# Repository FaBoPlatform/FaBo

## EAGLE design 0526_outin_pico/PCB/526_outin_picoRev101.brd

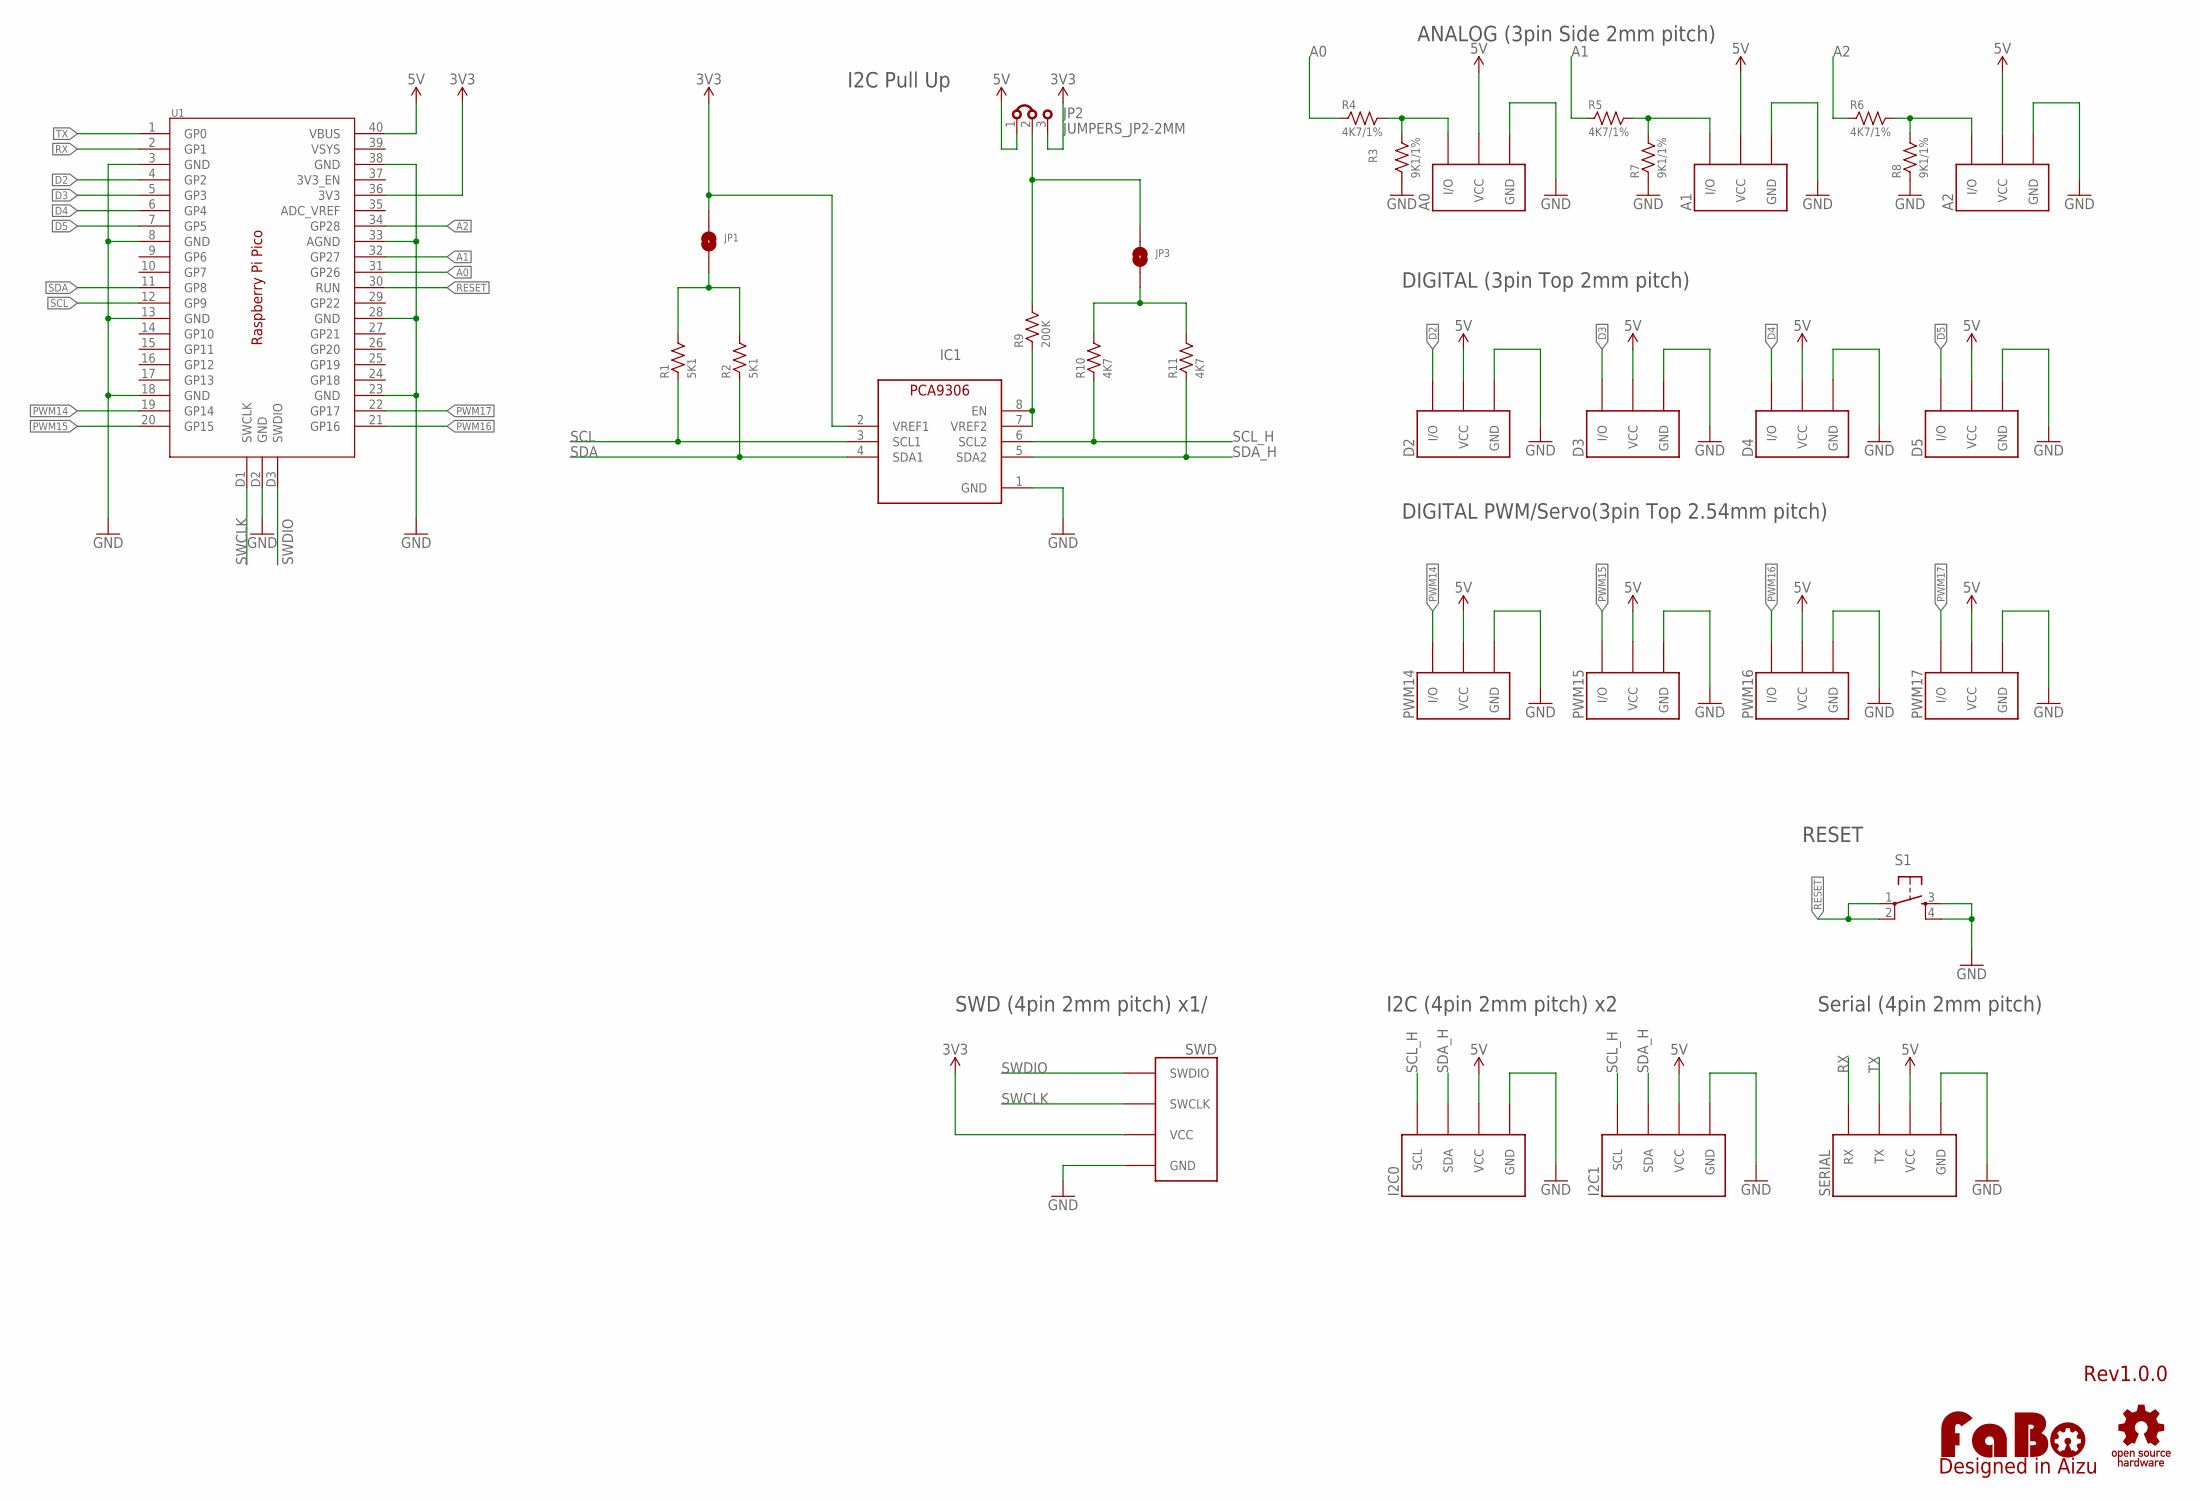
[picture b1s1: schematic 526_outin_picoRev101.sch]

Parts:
A0, A1, A2: FABO_BRICK_3PIN-S03B-PASK-2_LONG; FABO_BRICK_3PIN_S03B-PASK-2_LONG
D2, D3, D4, D5: FABO_BRICK_3PIN-B03B-PASK-1; FABO_BRICK_3PIN_B03B-PASK-1
I2C0, I2C1: FABO_BRICK_I2C-B04B-PASK-1; FABO_BRICK_I2C_B04B-PASK-1
IC1: PCA9306_SSOP; 8PIN-SSOP
JP1, JP3: SMD-JUMPER-2_SHORT; SMD-JUMPER-2-SHORT
JP2: JUMPERS_JP2-2MM
LOGO1: LOGO_OSHW-M_BOTTOM; LOGO_OSHW_M_BOTTOM
LOGO2: LOGO_FABO-M; LOGO_FABO_M
PWM14, PWM15, PWM16, PWM17: FABO_BRICK_3PIN-HEADER; FABO_BRICK_3PIN_HEADER
R1, R2: 5K1; 0603
R3, R7, R8: 9K1/1%; 0603
R4, R5, R6: 4K7/1%; 0603
R9: 200K; 0603
R10, R11: 4K7; 0603
S1: TACT-SWITCH-6MM; DTS_6_V
SERIAL: FABO_BRICK_SERIAL-B04B-PASK-1; FABO_BRICK_SERIAL_B04B-PASK-1
SWD: FABO-SWD-4PIN; FABO_BRICK_SWD_B04B-PASK-1_SILK
U1: RASPBERRY_PI_PICO; RASPBERRY_PI_PICO_SMD

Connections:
3V3: IC1.2 (VREF1), JP1.1, JP2.3, SWD.VCC, U1.36 (3V3)
5V: A0.VCC, A1.VCC, A2.VCC, D2.VCC, D3.VCC, D4.VCC, D5.VCC, I2C0.VCC, I2C1.VCC, JP2.1, PWM14.VCC, PWM15.VCC, PWM16.VCC, PWM17.VCC, SERIAL.VCC, U1.40 (VBUS)
A0: R4.1, U1.31 (GP26)
A1: R5.1, U1.32 (GP27)
A2: R6.1, U1.34 (GP28)
D2: D2.I/O, U1.4 (GP2)
D3: D3.I/O, U1.5 (GP3)
D4: D4.I/O, U1.6 (GP4)
D5: D5.I/O, U1.7 (GP5)
GND: A0.GND, A1.GND, A2.GND, D2.GND, D3.GND, D4.GND, D5.GND, I2C0.GND, I2C1.GND, IC1.1 (GND), PWM14.GND, PWM15.GND, PWM16.GND, PWM17.GND, R3.1, R7.1, R8.1, S1.3, S1.4, SERIAL.GND, SWD.GND, U1.3 (GND), U1.8 (GND), U1.13 (GND), U1.18 (GND), U1.23 (GND), U1.28 (GND), U1.33 (AGND), U1.38 (GND), U1.D2 (GND)
unnamed: A0.I/O, R3.2, R4.2
unnamed: A1.I/O, R5.2, R7.2
unnamed: JP1.2, R1.2, R2.2
unnamed: A2.I/O, R6.2, R8.2
unnamed: JP2.2, JP3.1, R9.2
unnamed: JP3.2, R10.2, R11.2
unnamed: IC1.7 (VREF2), IC1.8 (EN), R9.1
PWM14: PWM14.I/O, U1.19 (GP14)
PWM15: PWM15.I/O, U1.20 (GP15)
PWM16: PWM16.I/O, U1.21 (GP16)
PWM17: PWM17.I/O, U1.22 (GP17)
RESET: S1.1, S1.2, U1.30 (RUN)
RX: SERIAL.RX, U1.2 (GP1)
SCL: IC1.3 (SCL1), R1.1, U1.12 (GP9)
SCL_H: I2C0.SCL, I2C1.SCL, IC1.6 (SCL2), R10.1
SDA: IC1.4 (SDA1), R2.1, U1.11 (GP8)
SDA_H: I2C0.SDA, I2C1.SDA, IC1.5 (SDA2), R11.1
SWCLK: SWD.SWCLK, U1.D1 (SWCLK)
SWDIO: SWD.SWDIO, U1.D3 (SWDIO)
TX: SERIAL.TX, U1.1 (GP0)

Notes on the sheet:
Rev1.0.0
DIGITAL (3pin Top 2mm pitch)
ANALOG (3pin Side 2mm pitch)
DIGITAL PWM/Servo(3pin Top 2.54mm pitch)
I2C (4pin 2mm pitch) x2
Serial (4pin 2mm pitch)
RESET
I2C Pull Up
SWD (4pin 2mm pitch) x1/

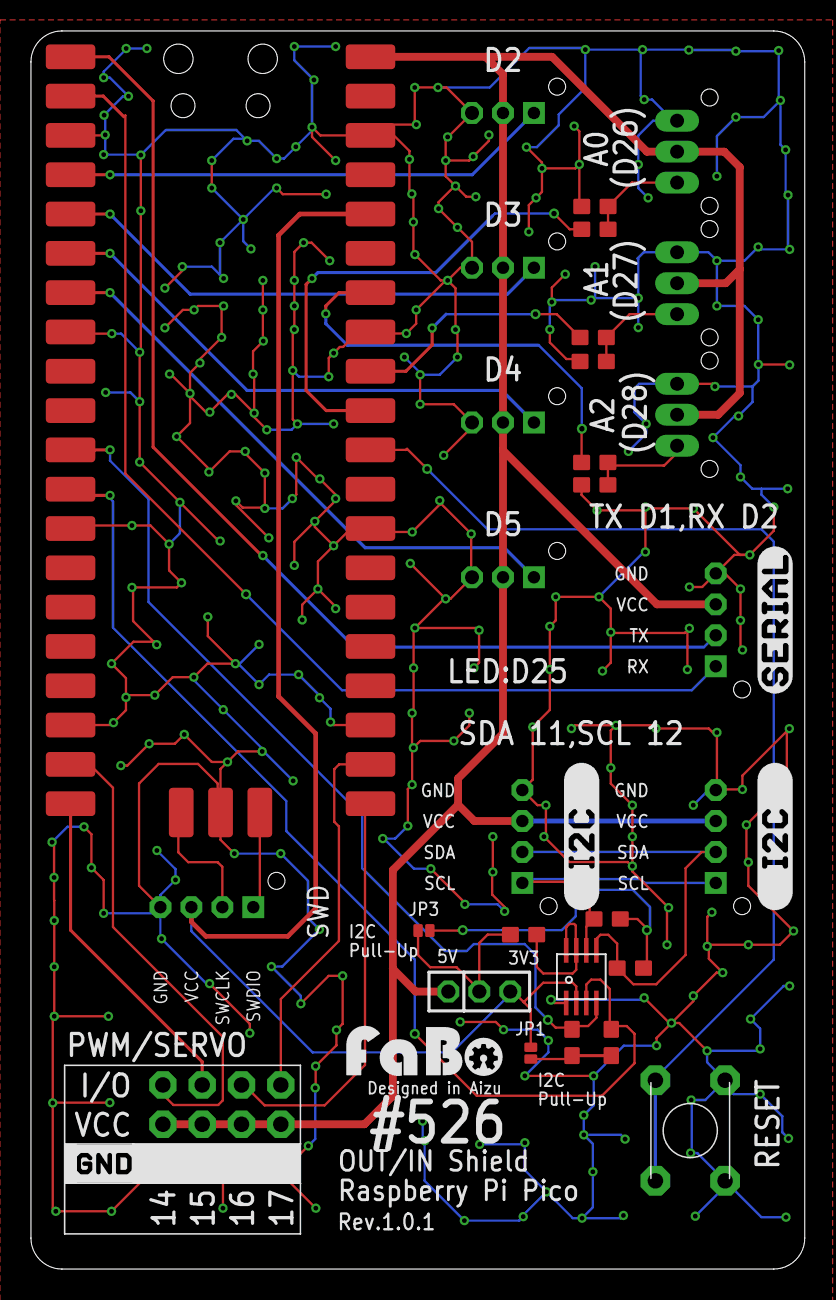
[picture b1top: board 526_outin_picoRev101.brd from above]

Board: 2 copper layers, 50.0 x 80.0 mm, 38 parts (0 on the bottom side), 30 nets.

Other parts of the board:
U$2: LOGO_SILK_SERIAL2
U$11, U$12: LOGO_SILK_I2C
U$19: LOGO_SILK_GND

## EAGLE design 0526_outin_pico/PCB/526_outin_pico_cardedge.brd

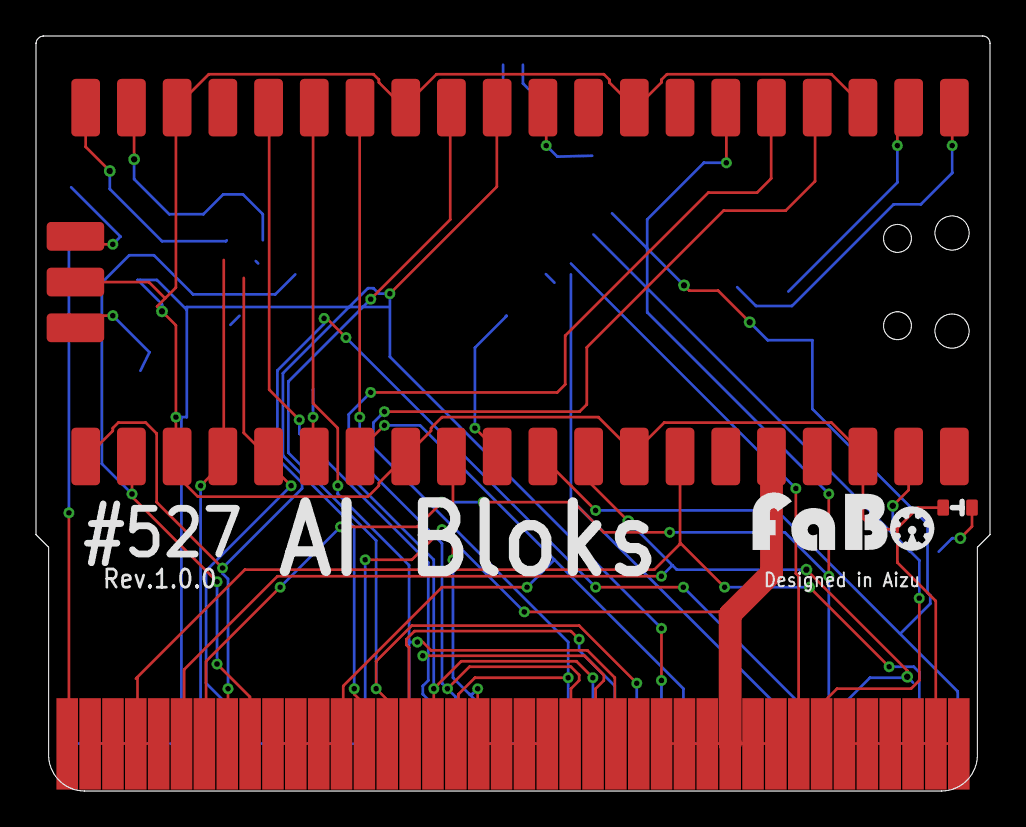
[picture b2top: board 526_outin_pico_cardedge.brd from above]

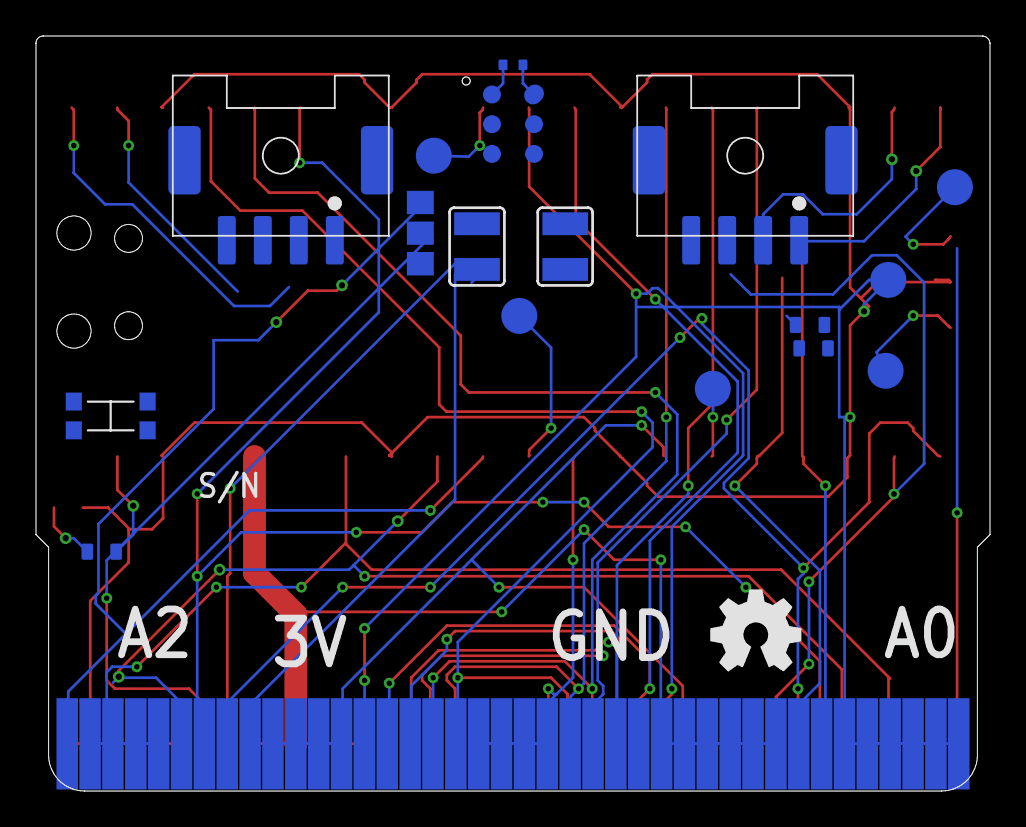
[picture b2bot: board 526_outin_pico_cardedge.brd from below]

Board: 2 copper layers, 53.0 x 41.9 mm, 22 parts (17 on the bottom side), 34 nets.

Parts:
C1: 0.1uF; 0402
CN1, CN2: SM04B-PASS
GP7: TPSQTP20R; TP20R
JMP1: 0R-JUMPA; A0R-JMP
LED1: 0603
LOGO1: LOGO_OSHW_M_BOTTOM
LOGO2: LOGO_FABO_M
R1: 470; 0603
R2, R3: 0603
S2: KMR2
SJ1, SJ2: SJW
TP1, TP2, TP3, TP4, TP10: TPSQTP20R; TP20R
U1: RASPBERRY_PI_PICO_SMD
U$1: SPM0405H; SPM4050
U$2: BBC_EDGE

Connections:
3V3: C1.2, CN1.3, CN2.3, JMP1.1, R2.2, R3.2, U1.36, U$1.6:VDD, U$2.P$27, U$2.P$28, U$2.P$29, U$2.P$30, U$2.P$31, U$2.P$32, U$2.P$67, U$2.P$68, U$2.P$69, U$2.P$70, U$2.P$71, U$2.P$72
A0: U1.31, U$2.P$1, U$2.P$41
A1: U1.32, U$2.P$6, U$2.P$46
A2: U1.34, U$2.P$2, U$2.P$3, U$2.P$4, U$2.P$5, U$2.P$42, U$2.P$43, U$2.P$44, U$2.P$45
D2: U1.4, U$2.P$18, U$2.P$58
D3: U1.5, U$2.P$17, U$2.P$57
D4: U1.6, U$2.P$7, U$2.P$47
D8: U1.11, U$2.P$14, U$2.P$54
D9_LEDS: U1.12, U$2.P$15, U$2.P$55
GND: C1.1, CN1.4, CN2.4, JMP1.3, LED1.CATHODE, S2.3, S2.4, TP3.TP, U1.3, U1.8, U1.13, U1.18, U1.23, U1.28, U1.33, U1.38, U1.D2, U$1.1:GND, U$1.3:GND, U$2.P$35, U$2.P$36, U$2.P$37, U$2.P$38, U$2.P$39, U$2.P$40, U$2.P$75, U$2.P$76, U$2.P$77, U$2.P$78, U$2.P$79, U$2.P$80
GP14: CN2.2, U1.19
GP15: CN2.1, U1.20
GP16: U$2.P$16, U$2.P$56
GP16_PWM_UART0_TX: U1.21, U$2.P$8, U$2.P$48
GP17_PWM_UART0_RX: U1.22, U$2.P$9, U$2.P$49
I2C1_SCL: R2.1, U1.25, U$2.P$33, U$2.P$73
I2C1_SDA: R3.1, U1.24, U$2.P$34, U$2.P$74
unnamed: R1.1, U1.39
unnamed: LED1.ANODE, R1.2
unnamed: GP7.TP, U1.10
unnamed: TP10.TP, U1.26
unnamed: JMP1.2, U$1.2:LEFT/RIGHT
unnamed: SJ1.1, U$1.4:CLOCK
unnamed: SJ2.1, U$1.5:DATA
PDM_CLK: SJ1.2, U1.27, U$2.P$10, U$2.P$11, U$2.P$12, U$2.P$13, U$2.P$50, U$2.P$51, U$2.P$52, U$2.P$53
PDM_DIN: SJ2.2, U1.29, U$2.P$19, U$2.P$20, U$2.P$21, U$2.P$22, U$2.P$59, U$2.P$60, U$2.P$61, U$2.P$62
RESET: S2.1, S2.2, TP4.TP, U1.30
RX: CN1.1, U1.2
SPI1_RX: U1.16, U$2.P$24, U$2.P$64
SPI1_SCK: U1.14, U$2.P$23, U$2.P$63
SPI1_TX: U1.15, U$2.P$25, U$2.P$65
SWCLK: TP1.TP, U1.D1
SWDIO: TP2.TP, U1.D3
TX: CN1.2, U1.1

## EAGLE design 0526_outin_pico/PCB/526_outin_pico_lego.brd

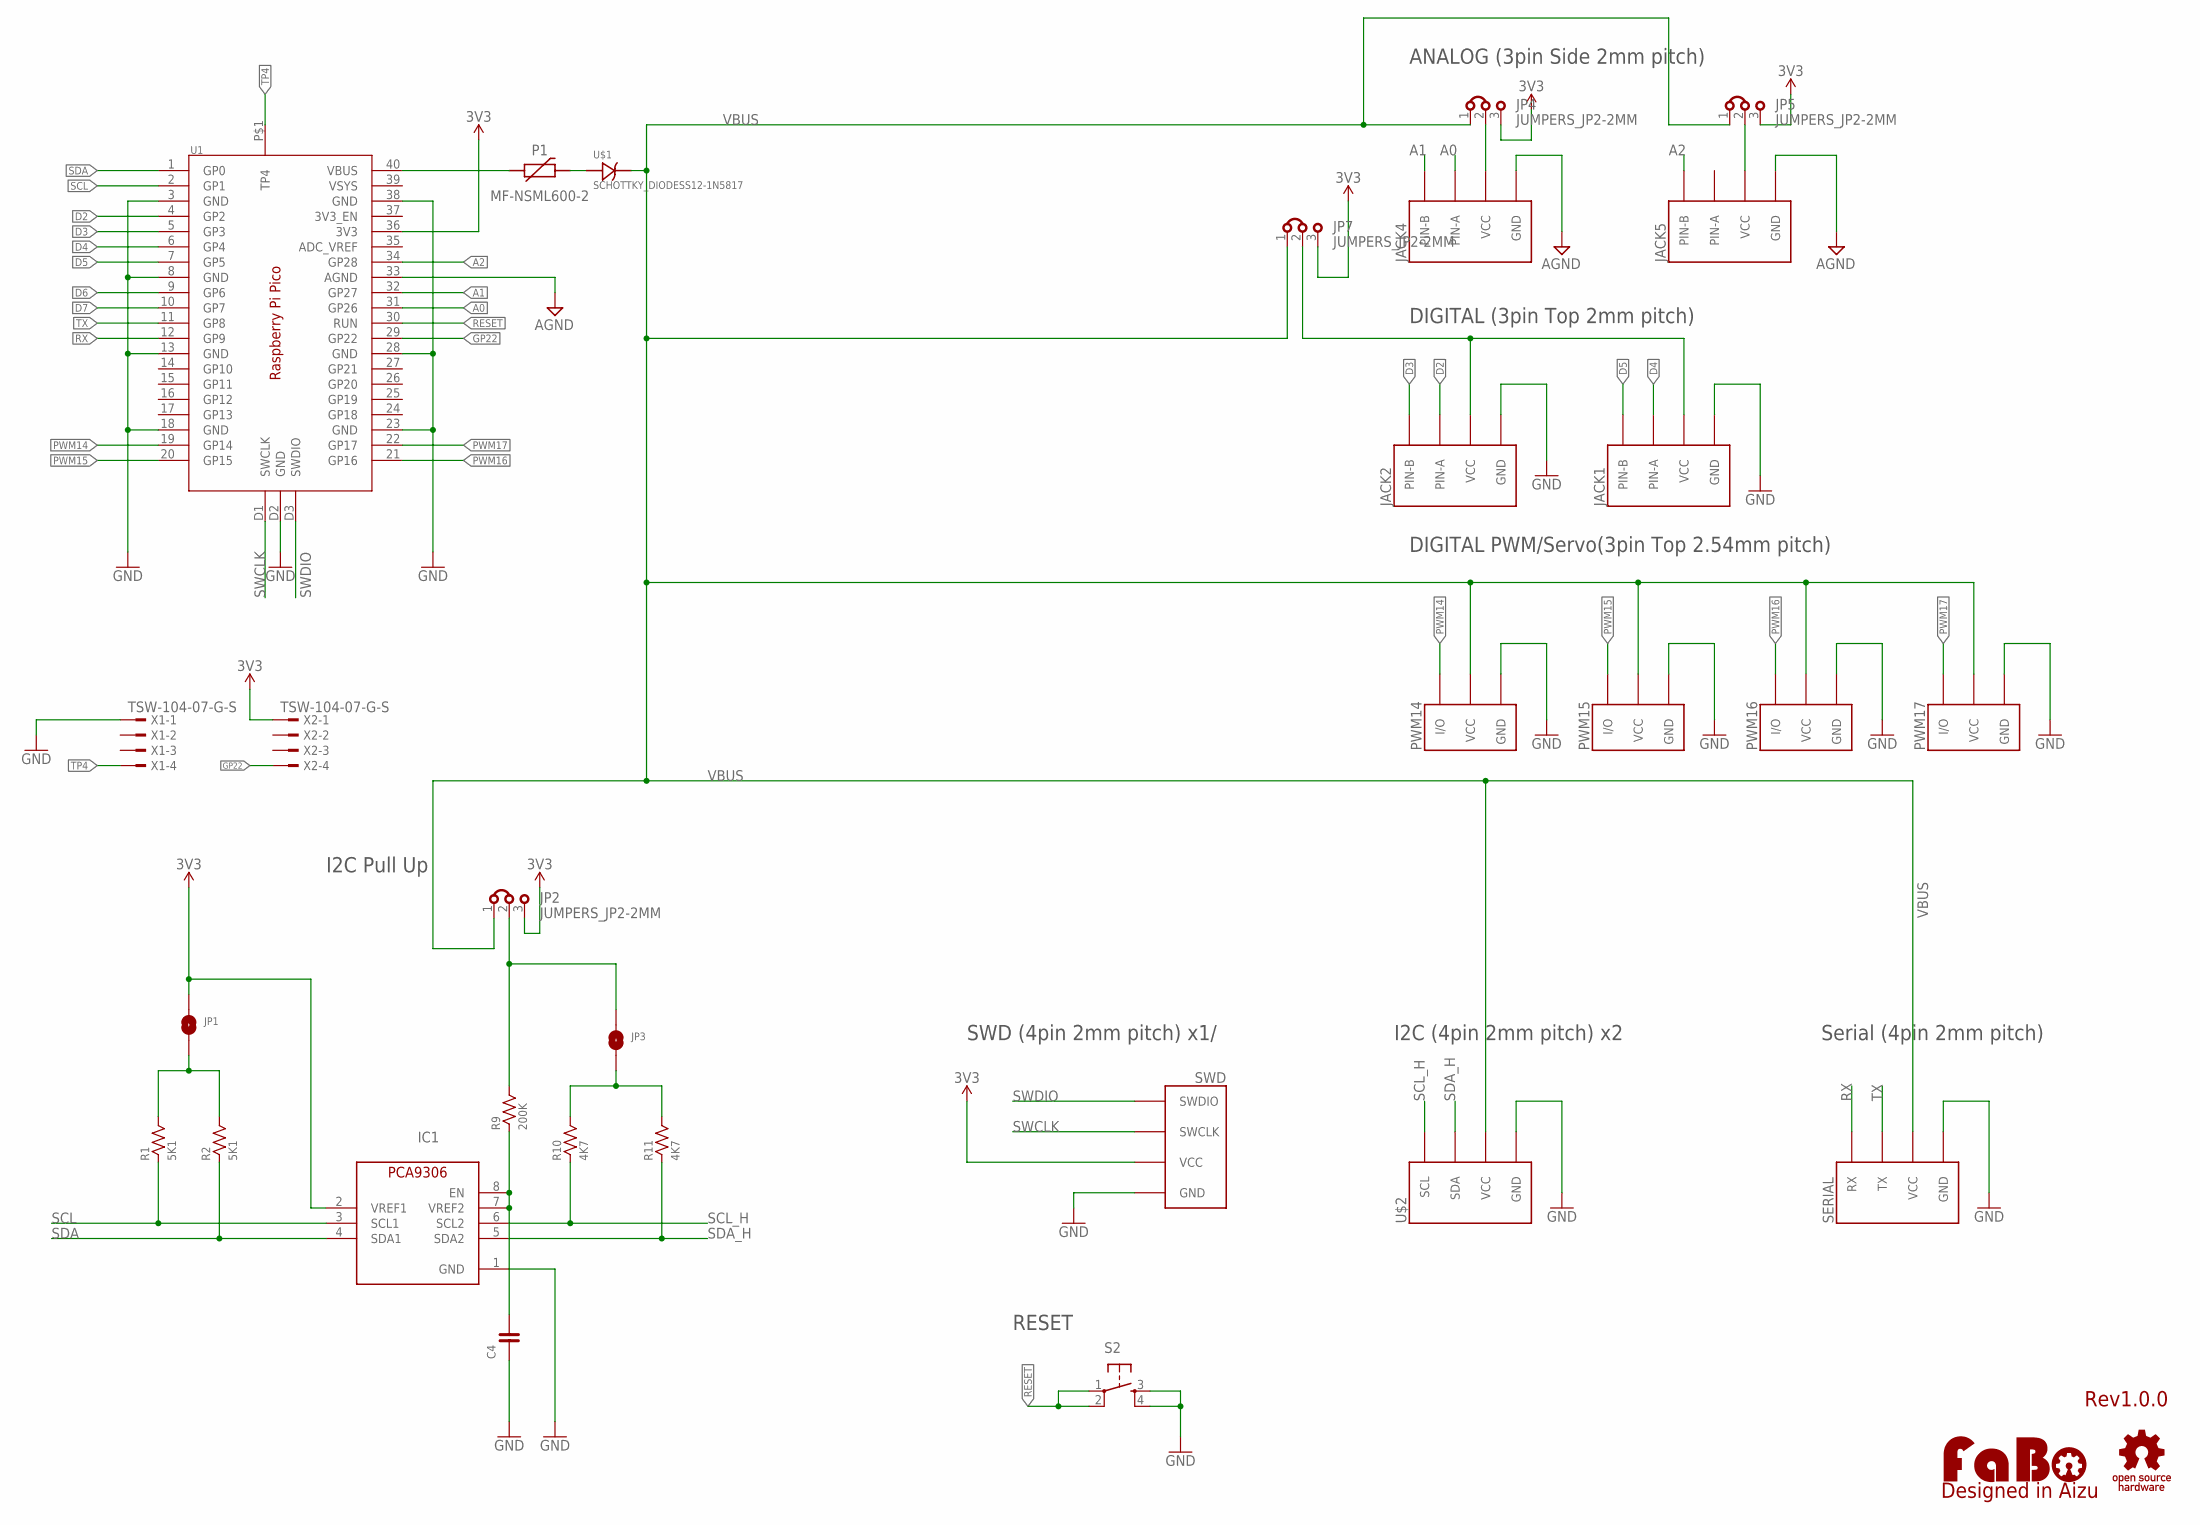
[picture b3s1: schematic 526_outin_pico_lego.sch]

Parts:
C4: CAPACITOR-0603_NARROW; 0603-NARROW
IC1: PCA9306_SSOP; 8PIN-SSOP
JACK1, JACK2, JACK4, JACK5: MODULAR-JACK-6P; 7002-6PXC-X
JP1, JP3: SMD-JUMPER-2_SHORT; SMD-JUMPER-2-SHORT
JP2, JP4, JP5, JP7: JUMPERS_JP2-2MM
LOGO1: LOGO_OSHW-M_BOTTOM; LOGO_OSHW_M_BOTTOM
LOGO2: LOGO_FABO-M; LOGO_FABO_M
P1: MF-NSML600-2; 1206
PWM14, PWM15, PWM16, PWM17: FABO_BRICK_3PIN-HEADER; FABO_BRICK_3PIN_HEADER
R1, R2: 5K1; 0603
R9: 200K; 0603
R10, R11: 4K7; 0603
S2: TACT-SWITCH-SMD_KMR2; KMR2
SERIAL: FABO_BRICK_SERIAL-S04B-PASK-2_LONG; FABO_BRICK_SERIAL_S04B-PASK-2_LONG
SWD: FABO-SWD-4PIN; FABO_BRICK_SWD_B04B-PASK-1_SILK
U1: RASPBERRY_PI_PICORASPBERRY_PI_PICO_SMD_PDM; RASPBERRY_PI_PICO_SMD_PDM
U$1: SCHOTTKY_DIODESS12-1N5817; DO-214AC
U$2: MODULAR-JACK-6P-I2C; 7002-6PXC-X
X1, X2: TSW-104-07-G-S; TSW-104-XX-G-S

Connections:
3V3: IC1.2 (VREF1), JP1.1, JP2.3, JP4.3, JP5.3, JP7.3, SWD.VCC, U1.36 (3V3), X2.1
A0: JACK4.5 (PIN-A), U1.31 (GP26)
A1: JACK4.6 (PIN-B), U1.32 (GP27)
A2: JACK5.6 (PIN-B), U1.34 (GP28)
AGND: JACK4.1 (GND), JACK5.1 (GND), U1.33 (AGND)
D2: JACK2.5 (PIN-A), U1.4 (GP2)
D3: JACK2.6 (PIN-B), U1.5 (GP3)
D4: JACK1.5 (PIN-A), U1.6 (GP4)
D5: JACK1.6 (PIN-B), U1.7 (GP5)
D6: U1.9 (GP6)
D7: U1.10 (GP7)
GND: C4.1, IC1.1 (GND), JACK1.1 (GND), JACK2.1 (GND), PWM14.GND, PWM15.GND, PWM16.GND, PWM17.GND, S2.3, S2.4, SERIAL.GND, SWD.GND, U1.3 (GND), U1.8 (GND), U1.13 (GND), U1.18 (GND), U1.23 (GND), U1.28 (GND), U1.38 (GND), U1.D2 (GND), U$2.1 (GND), X1.1
GP22: U1.29 (GP22), X2.4
unnamed: JACK5.3 (VCC), JP5.2
unnamed: JP1.2, R1.2, R2.2
unnamed: JACK4.3 (VCC), JP4.2
unnamed: JACK1.3 (VCC), JACK2.3 (VCC), JP7.2
unnamed: P1.P$2 (2), U$1.CATHODE (ANODE)
unnamed: JP2.2, JP3.1, R9.2
unnamed: JP3.2, R10.2, R11.2
unnamed: C4.2, IC1.7 (VREF2), IC1.8 (EN), R9.1
PWM14: PWM14.I/O, U1.19 (GP14)
PWM15: PWM15.I/O, U1.20 (GP15)
PWM16: PWM16.I/O, U1.21 (GP16)
PWM17: PWM17.I/O, U1.22 (GP17)
RESET: S2.1, S2.2, U1.30 (RUN)
RX: SERIAL.RX, U1.12 (GP9)
SCL: IC1.3 (SCL1), R1.1, U1.2 (GP1)
SCL_H: IC1.6 (SCL2), R10.1, U$2.4 (SCL)
SDA: IC1.4 (SDA1), R2.1, U1.1 (GP0)
SDA_H: IC1.5 (SDA2), R11.1, U$2.5 (SDA)
SWCLK: SWD.SWCLK, U1.D1 (SWCLK)
SWDIO: SWD.SWDIO, U1.D3 (SWDIO)
TP4: U1.P$1 (TP4), X1.4
TX: SERIAL.TX, U1.11 (GP8)
VBUS: JP2.1, JP4.1, JP5.1, JP7.1, PWM14.VCC, PWM15.VCC, PWM16.VCC, PWM17.VCC, SERIAL.VCC, U$1.ANODE (CATHODE), U$2.3 (VCC)
VS: P1.P$1 (1), U1.40 (VBUS)

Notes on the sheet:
Rev1.0.0
DIGITAL (3pin Top 2mm pitch)
ANALOG (3pin Side 2mm pitch)
DIGITAL PWM/Servo(3pin Top 2.54mm pitch)
I2C (4pin 2mm pitch) x2
Serial (4pin 2mm pitch)
RESET
I2C Pull Up
SWD (4pin 2mm pitch) x1/

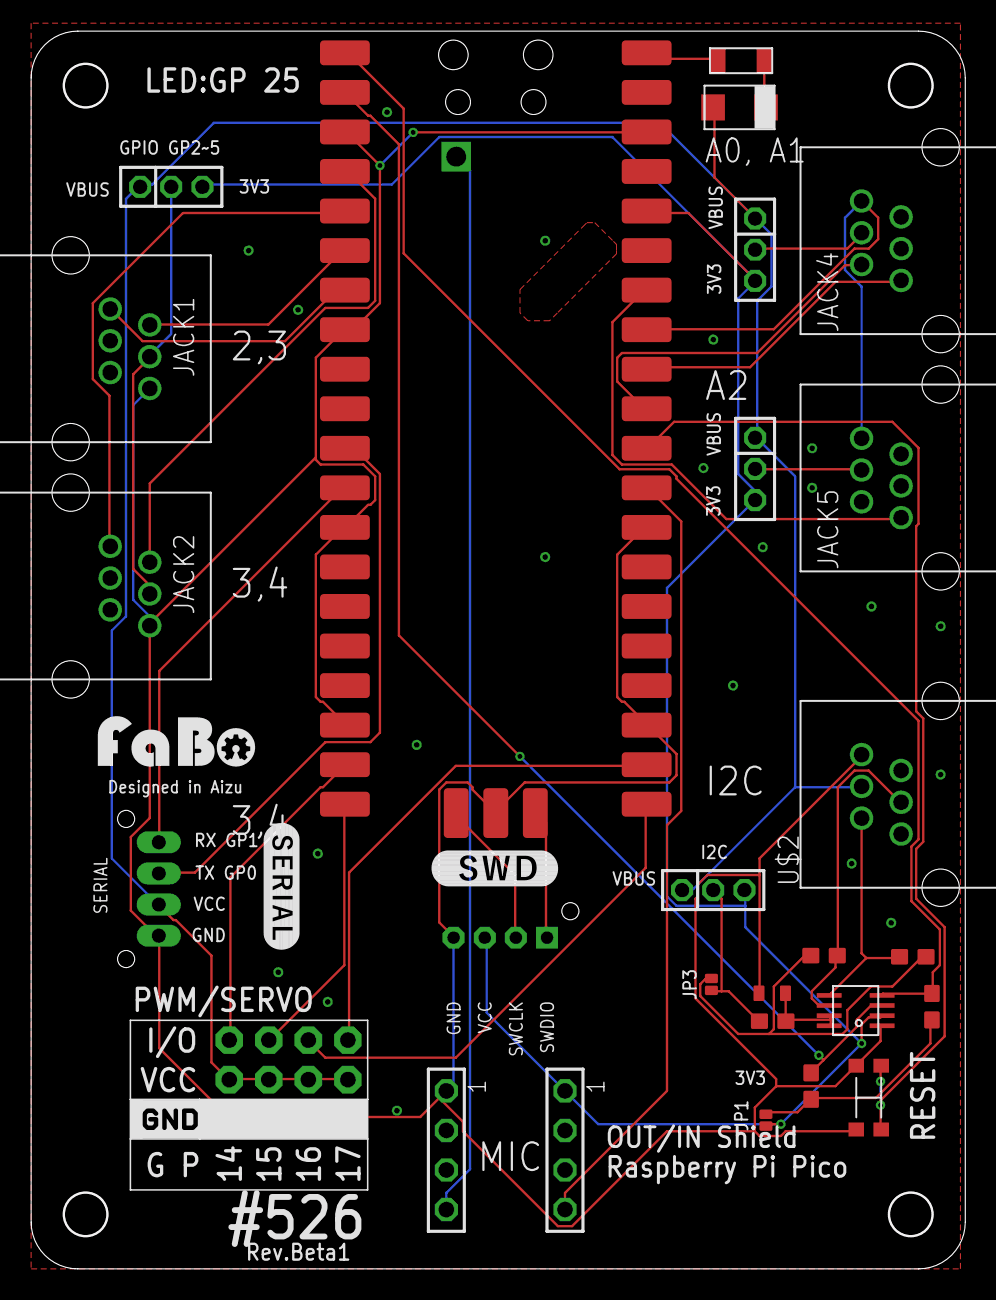
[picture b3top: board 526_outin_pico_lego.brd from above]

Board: 2 copper layers, 60.0 x 79.5 mm, 33 parts (0 on the bottom side), 35 nets.

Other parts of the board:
U$19: LOGO_SILK_GND

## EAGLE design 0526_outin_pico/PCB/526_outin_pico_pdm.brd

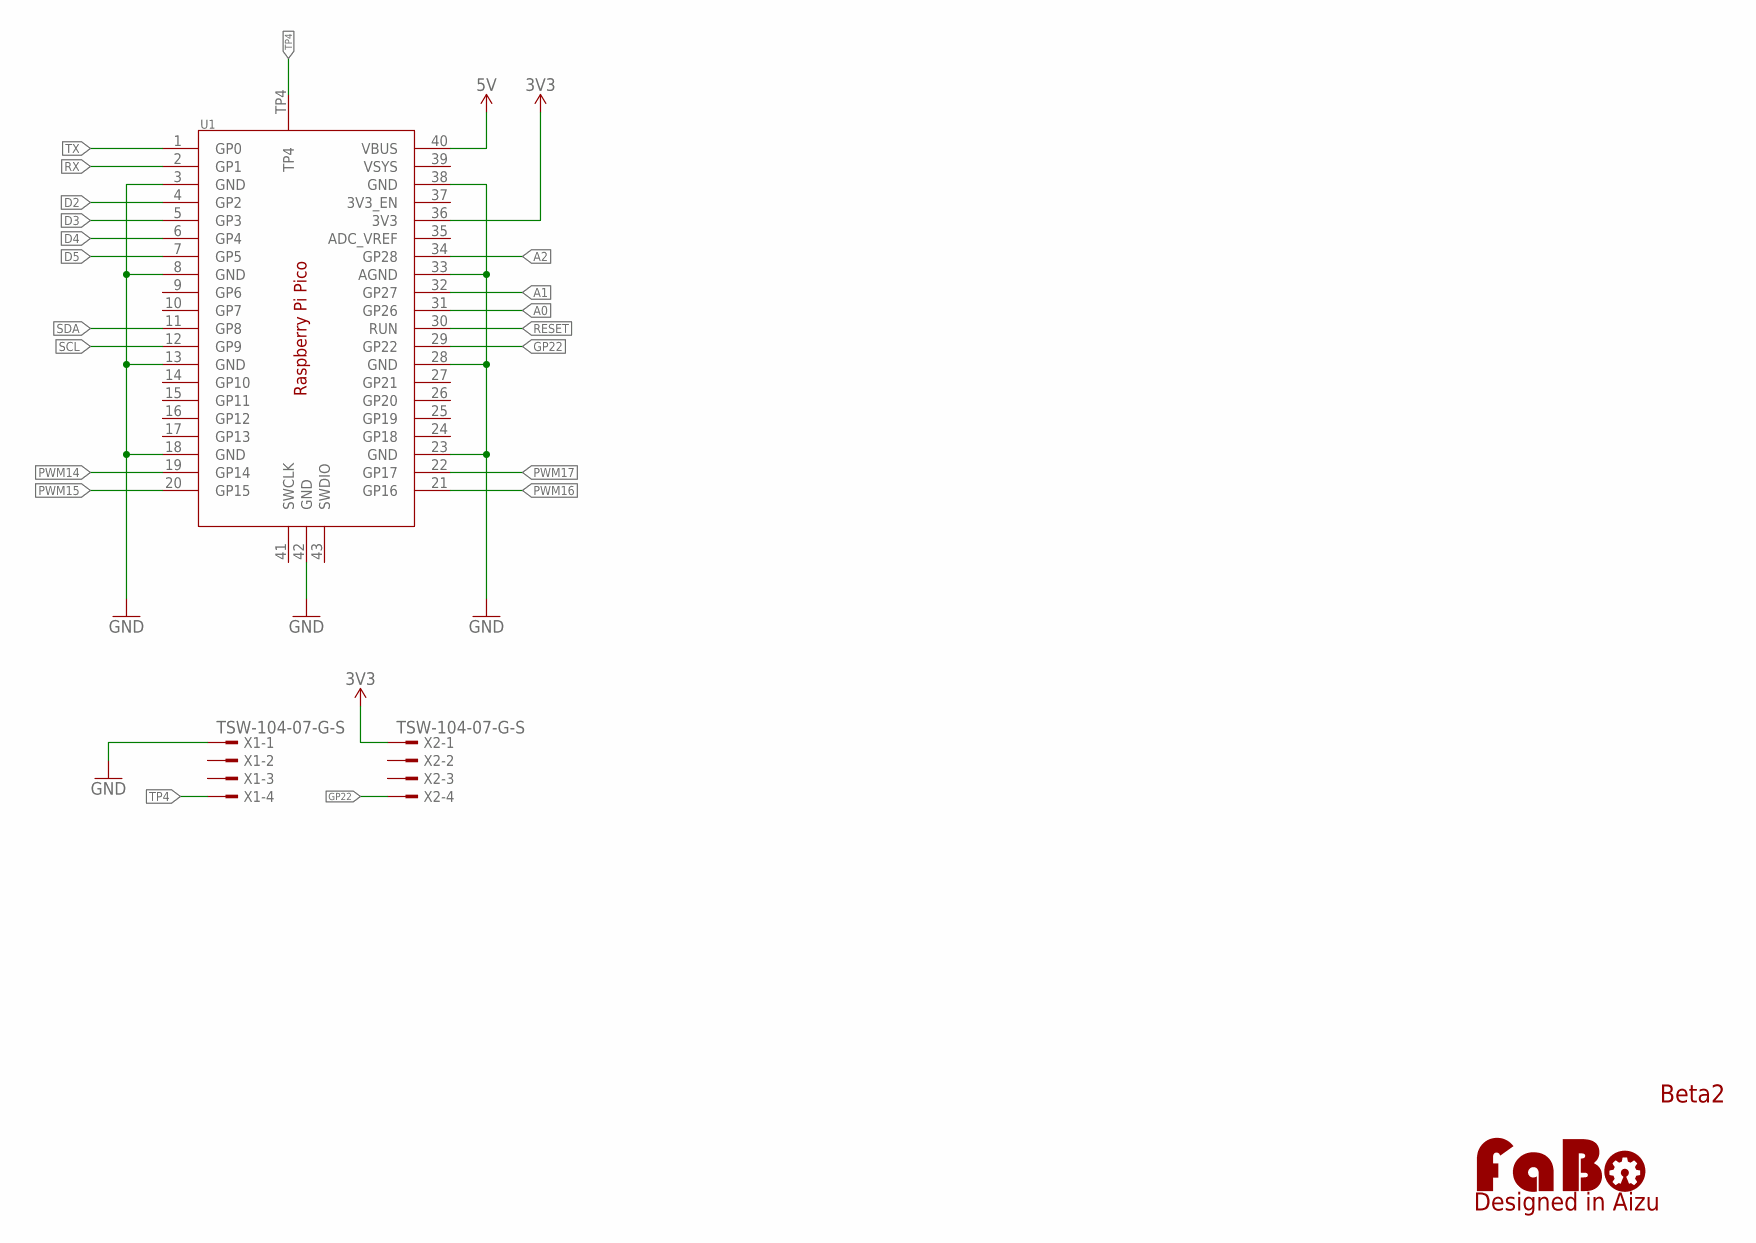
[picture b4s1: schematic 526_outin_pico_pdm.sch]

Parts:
LOGO2: LOGO_FABO-M; LOGO_FABO_M
U1: RASPBERRY_PI_PICOPDM; RASPBERRY_PI_PICO_HEADER
X1, X2: TSW-104-07-G-S; TSW-104-XX-G-S

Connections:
3V3: U1.36 (3V3), X2.1
5V: U1.40 (VBUS)
A0: U1.31 (GP26)
A1: U1.32 (GP27)
A2: U1.34 (GP28)
D2: U1.4 (GP2)
D3: U1.5 (GP3)
D4: U1.6 (GP4)
D5: U1.7 (GP5)
GND: U1.3 (GND), U1.8 (GND), U1.13 (GND), U1.18 (GND), U1.23 (GND), U1.28 (GND), U1.33 (AGND), U1.38 (GND), U1.42 (GND), X1.1
GP22: U1.29 (GP22), X2.4
PWM14: U1.19 (GP14)
PWM15: U1.20 (GP15)
PWM16: U1.21 (GP16)
PWM17: U1.22 (GP17)
RESET: U1.30 (RUN)
RX: U1.2 (GP1)
SCL: U1.12 (GP9)
SDA: U1.11 (GP8)
TP4: U1.TP4, X1.4
TX: U1.1 (GP0)

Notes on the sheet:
Beta2

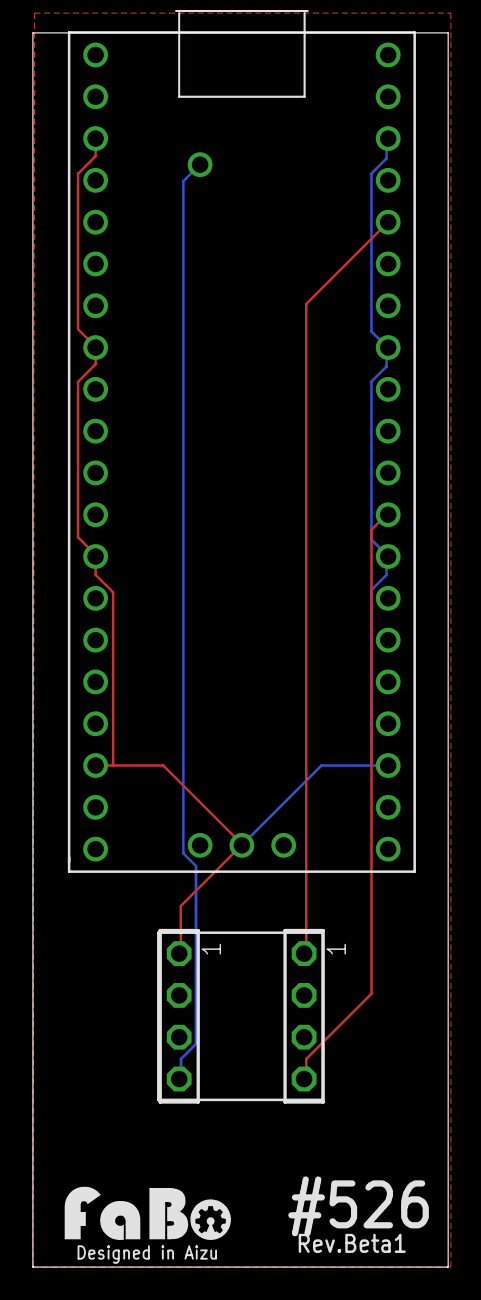
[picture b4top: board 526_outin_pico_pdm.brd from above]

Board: 2 copper layers, 25.2 x 75.0 mm, 4 parts (0 on the bottom side), 4 nets.

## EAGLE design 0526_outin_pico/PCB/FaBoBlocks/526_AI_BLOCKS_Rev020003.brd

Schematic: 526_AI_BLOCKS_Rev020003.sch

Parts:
ANALOG(GP26,GP27,GP28): MODULAR-JACK-6P-RJ11_ANALOG3; 7002-6PXC-X
C1, C7: 22uF/0805; 0805
C2: 1uF; 0603
C3: 10pF; 0603
C4: DNP; 0603
C5, C6, C8: 0.1uF; 0603
C9: 10uF; 0603
D1: SR54F; SMBF
GP2,GP3,GP6, GP7,GP10,GP11, GP20,GP21,GP22: MODULAR-JACK-6P-RJ11_GPIO3; 7002-6PXC-X
I2C1(GP4,GP5): MODULAR-JACK-6P-RJ11_I2C; 7002-6PXC-X
J2: FABO_BRICK_2PIN; FABO_BRICK_2PIN_B02B-PASK-1_SILK
L1: 744316470
LED1: RED; 0603
LOGO1: LOGO_OSHW-M_BOTTOM; LOGO_OSHW_M_BOTTOM
LOGO2: LOGO_FABO-M; LOGO_FABO_M
P1: MF-NSML300-2; 1206
PWM12_SPI1_MISO, PWM13_SPI1_SS, PWM14_SPI1_SCK, PWM15_SPI1_MOSI: FABO_BRICK_3PIN-HEADER; FABO_BRICK_3PIN_HEADER
R1: 1K/0805; 0805
R2: 10; 0603
R3, R10, R11: 100K; 0603
R4: 47K/1% Thick Res; 0603
R5: 40.2K/1% Thick Res; 0603
R6: 7.68K/1% Thick Res; 0603
R7: 10/1% Thick Res; 0603
R8: 330; 0603
R9: 20K; 0603
R12, R13: DNP/0805; 0805
R14, R15: 4.7K/0805; 0805
RESET: TS-06104
SPI0(GP16,GP17,GP18,GP19): MODULAR-JACK-6P-RJ11_SPI; 7002-6PXC-X
SW, SW1: TPB1,27; B1,27
U2: MP1476L; SOT563
U$1, U$8, U$9, U$11: SSSS213202
U$4, U$5, U$6, U$7: BLOCK_4-1; 4-1BLOCK
U$10: RASPBERRY_PI_PICO_BOTH_TH_PINHEADER; RASPBERRY_PI_PICO_HEADER_BOTH
U$17: TPS2113A; VSON8
UART0(GP0,GP1), UART1(GP8,GP9): MODULAR-JACK-6P-RJ11_SERIAL_M; 7002-6PXC-X

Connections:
3V3: C8.2, R12.2, R13.2, R14.2, R15.2, U$1.3, U$8.3, U$10.36 (3V3), U$10.68, U$17.8 (8:IN1)
3V3_EN: U$10.37 (3V3_EN), U$10.67
ADC_VREF: U$10.35 (ADC_VREF), U$10.69
AGND: ANALOG(GP26,GP27,GP28).1 (1:GND), U$10.33 (AGND), U$10.71
BLOCKS_GPIO_5V: C9.2, GP2,GP3,GP6.3 (3:VCC), GP7,GP10,GP11.3 (3:VCC), GP20,GP21,GP22.3 (3:VCC), R11.1, U$17.7 (7:OUT), UART1(GP8,GP9).3 (3:VCC)
GND: C1.1, C4.1, C5.1, C6.1, C7.1, C8.1, C9.1, GP2,GP3,GP6.1 (1:GND), GP7,GP10,GP11.1 (1:GND), GP20,GP21,GP22.1 (1:GND), I2C1(GP4,GP5).1 (1:GND), J2.GND1 (GND), PWM12_SPI1_MISO.GND, PWM13_SPI1_SS.GND, PWM14_SPI1_SCK.GND, PWM15_SPI1_MOSI.GND, R1.2, R6.1, R8.1, R9.1, R10.1, RESET.C, RESET.D, SPI0(GP16,GP17,GP18,GP19).1 (1:GND), U2.3:GND, U$10.3 (GND), U$10.8 (GND), U$10.13 (GND), U$10.18 (GND), U$10.23 (GND), U$10.28 (GND), U$10.38 (GND), U$10.42 (GND), U$10.46, U$10.51, U$10.56, U$10.61, U$10.66, U$10.76, U$10.81, U$10.85 (GND), U$11.3, U$17.5 (5:GND), U$17.9 (5:GND), U$17.P$1 (5:GND), U$17.P$2 (5:GND), U$17.P$3 (5:GND), U$17.P$4 (5:GND), UART0(GP0,GP1).1 (1:GND), UART1(GP8,GP9).1 (1:GND)
GP0: U$10.1 (GP0), U$10.44, UART0(GP0,GP1).5 (5:TX)
GP1: U$10.2 (GP1), U$10.45, UART0(GP0,GP1).6 (6:RX)
GP2: GP2,GP3,GP6.5 (5:PIN-A), U$10.4 (GP2), U$10.47
GP3: GP2,GP3,GP6.4 (4:PIN-C), U$10.5 (GP3), U$10.48
GP4: I2C1(GP4,GP5).5 (5:SDA), R14.1, U$10.6 (GP4), U$10.49
GP5: I2C1(GP4,GP5).4 (4:SCL), R15.1, U$10.7 (GP5), U$10.50
GP6: GP2,GP3,GP6.6 (6:PIN-B), U$10.9 (GP6), U$10.52
GP7: GP7,GP10,GP11.6 (6:PIN-B), U$10.10 (GP7), U$10.53
GP8: U$10.11 (GP8), U$10.54, UART1(GP8,GP9).5 (5:TX)
GP9: U$10.12 (GP9), U$10.55, UART1(GP8,GP9).6 (6:RX)
GP10: GP7,GP10,GP11.5 (5:PIN-A), U$10.14 (GP10), U$10.57
GP11: GP7,GP10,GP11.4 (4:PIN-C), U$10.15 (GP11), U$10.58
GP12: PWM12_SPI1_MISO.I/O, U$10.16 (GP12), U$10.59
GP13: PWM13_SPI1_SS.I/O, U$10.17 (GP13), U$10.60
GP14: PWM14_SPI1_SCK.I/O, U$10.19 (GP14), U$10.62
GP15: PWM15_SPI1_MOSI.I/O, U$10.20 (GP15), U$10.63
GP16: SPI0(GP16,GP17,GP18,GP19).4 (4:MISO), U$10.21 (GP16), U$10.83
GP17: SPI0(GP16,GP17,GP18,GP19).6 (6:MOSI), U$10.22 (GP17), U$10.82
GP18: SPI0(GP16,GP17,GP18,GP19).2 (2:SCK), U$10.24 (GP18), U$10.80
GP19: SPI0(GP16,GP17,GP18,GP19).5 (5:CS), U$10.25 (GP19), U$10.79
GP20: GP20,GP21,GP22.5 (5:PIN-A), U$10.26 (GP20), U$10.78
GP21: GP20,GP21,GP22.4 (4:PIN-C), U$10.27 (GP21), U$10.77
GP22: GP20,GP21,GP22.6 (6:PIN-B), U$10.29 (GP22), U$10.75
GP26(A0): ANALOG(GP26,GP27,GP28).5 (5:A0), U$10.31 (GP26), U$10.73
GP27(A1): ANALOG(GP26,GP27,GP28).4 (4:A2), R13.1, U$10.32 (GP27), U$10.72
GP28(A2): ANALOG(GP26,GP27,GP28).6 (6:A1), R12.1, U$10.34 (GP28), U$10.70
IN_BAT1: J2.VCC, P1.2
IN_BAT2: C6.2, C7.2, P1.1, R3.1, SW1.TP, U2.1:IN (1:VIN)
unnamed: LED1.CATHODE, R1.1
unnamed: ANALOG(GP26,GP27,GP28).3 (3:VCC), U$1.2
unnamed: I2C1(GP4,GP5).3 (3:VCC), SPI0(GP16,GP17,GP18,GP19).3 (3:VCC), U$8.2, UART0(GP0,GP1).3 (3:VCC)
unnamed: R8.2, U$17.4 (4:ILIM)
unnamed: U$9.2, U$17.3 (3:VSNS)
unnamed: R9.2, U$9.3
unnamed: R10.2, U$17.2 (2:EN)
unnamed: R2.1, U2.4:BST
unnamed: C2.2, R2.2
unnamed: C4.2, R4.1, U2.6:FB
unnamed: R11.2, U$17.1 (1:STAT)
unnamed: C1.2, D1.ANODE, L1.2, R7.1
unnamed: C3.1, R4.2, R5.1, R6.2
unnamed: C3.2, R5.2, R7.2
PICO_5V: C5.2, D1.CATHODE, LED1.ANODE, PWM12_SPI1_MISO.VCC, PWM13_SPI1_SS.VCC, PWM14_SPI1_SCK.VCC, PWM15_SPI1_MOSI.VCC, U$1.1, U$8.1, U$9.1, U$10.39 (VSYS), U$10.65, U$17.6 (6:IN2)
POWERON: R3.2, U2.5:EN, U$11.2
RESET: RESET.A, RESET.B, U$10.30 (RUN), U$10.74
SWCLK: U$10.41 (SWCLK), U$10.84 (SWCLK1)
SWDIO: U$10.43 (SWDIO), U$10.86 (SWDIO1)
SW_OUT: C2.1, L1.1, SW.TP, U2.2:SW
VBUS: U$10.40 (VBUS), U$10.64

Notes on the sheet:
2.0.3
RESET
SSSS213202
Servo (3pin 2.54mm pitch)
4.7uH
BAT Uses 6 alkaline batteries
5.5V
5.0V
Revision
DC/DC StepDown AA BAT(6V~9V)->5V
INPUT ANALOG BLOCKS
SPI1,I2C1,Seral
GPIO INPUT/OUTPUT,PowerMUX
Raspberry Pi Pico,RESET,BLOCK
SERIAL1
SERIAL2
WIRE0
SPI0
ANALOG/WIRE1
GP2,3,6
GP7,10,11
GP20,21,22
PWM/SPI1
MAX 0.3A 6V
2.8~5.5V 1.25A(2A)
3.9~18V 800kHz StepDown IQ 190uA SCP,OVP,UVP 2A

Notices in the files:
parts and their libraries:
FaBo-Template: Released under the Creative Commons Attribution-ShareAlike 4.0 License
https://creativecommons.org/licenses/by-sa/4.0
FaBo-Symbol: Released under the Creative Commons
